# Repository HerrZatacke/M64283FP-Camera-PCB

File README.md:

# M64283FP Camera PCB

A PCB for mounting the M64283FP sensor to use it with a regular GameBoy Camera

With the revision from [24. Aug 2023](#24-aug-2023) it acts also as a good improvement against lightleaks when using the regular sensor ([Note this](#disclaimer)). 

This KiCad Project aims to replace the original GameBoy Camera Sensor PCB to allow using the alternative M64283FP sensor including accessing it's two extra pins `TADD` and `STRB`

## License
[MIT](LICENSE)

## Revision History
### 24. Aug 2023
  * Added Solderpoints for GND and VOUT
  * Changed PCB Shape to prevent light leaking
  * Changed footprints to prevent
### [08. Aug 2023](https://github.com/HerrZatacke/M64283FP-Camera-PCB/tree/d5482509ec9628336e77a40f23f6922016d4d017)
  * Initial Version

## Disclaimer
Attempt all modifications at your own risk. All sensors are highly sensitive to excessive heat. SMD projects are not for beginners. Use common sense. 

## Links
- Thanks to [Raphaël Boichot](https://github.com/Raphael-Boichot/) for starting the project.
- Visit the [Game Boy Gamera Club Discord](https://discord.gg/C7WFJHG) for discussions.
- Mitsubishi [M64282FP Sensor Datasheet](https://pdf1.alldatasheet.com/datasheet-pdf/view/146598/MITSUBISHI/M64282FP.html) (original sensor)
- Mitsubishi [M64283FP Sensor Datasheet](https://pdf1.alldatasheet.com/datasheet-pdf/view/89637/MITSUBISHI/M64283FP.html) (replacement sensor)

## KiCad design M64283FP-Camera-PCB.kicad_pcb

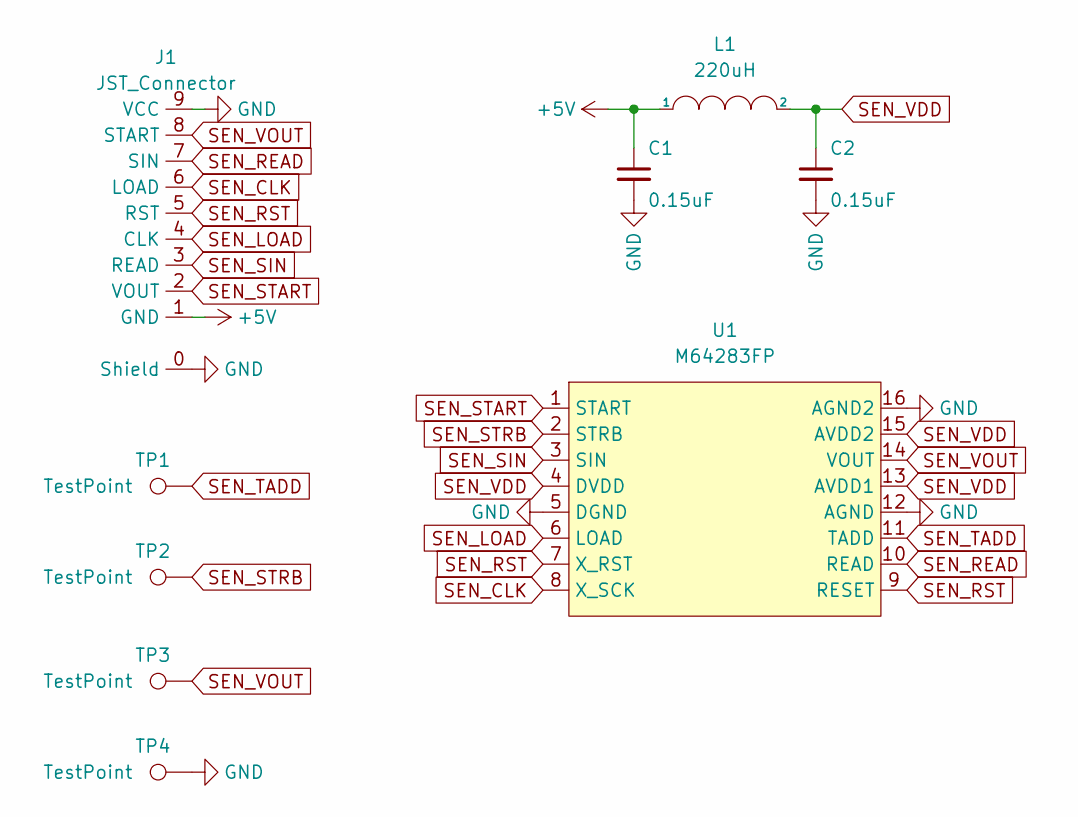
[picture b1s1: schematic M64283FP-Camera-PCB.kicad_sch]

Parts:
C1, C2: 0.15uF; 0603_HandSolder (LP)
J1: JST_Connector; JST Connector (LP)
L1: 220uH; 1210_HandSolder (LP)
TP1, TP2, TP3, TP4: TestPoint; TestPoint_Pad_1.5x1.5mm (LP)
U1: M64283FP; M6428xFP (LP)

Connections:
+5V: C1.1, J1.1 (GND), L1.1
GND: C1.2, C2.2, J1.0 (Shield), J1.9 (VCC), TP4.1, U1.5 (DGND), U1.12 (AGND), U1.16 (AGND2)
SEN_CLK: J1.6 (LOAD), U1.8 (X_SCK)
SEN_LOAD: J1.4 (CLK), U1.6 (LOAD)
SEN_READ: J1.7 (SIN), U1.10 (READ)
SEN_RST: J1.5 (RST), U1.7 (X_RST), U1.9 (RESET)
SEN_SIN: J1.3 (READ), U1.3 (SIN)
SEN_START: J1.2 (VOUT), U1.1 (START)
SEN_STRB: TP2.1, U1.2 (STRB)
SEN_TADD: TP1.1, U1.11 (TADD)
SEN_VDD: C2.1, L1.2, U1.4 (DVDD), U1.13 (AVDD1), U1.15 (AVDD2)
SEN_VOUT: J1.8 (START), TP3.1, U1.14 (VOUT)

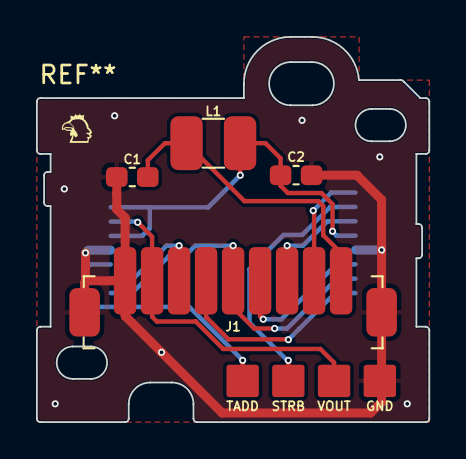
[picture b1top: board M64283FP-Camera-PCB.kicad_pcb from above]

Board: 2 copper layers, 21.8 x 21.4 mm, 9 parts (1 on the bottom side), 12 nets.

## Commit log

2023-08-07 Initial project data
2023-08-07 Add logo
2023-08-07 Add preview image Optimize labels
2023-08-07 Add Readme
2023-08-24 Add LightProof (LP) footprints
2023-08-24 Update Logo
2023-08-24 Update project with new footprints and PCB shape
2023-08-24 Caches
2023-08-24 Fix link
2023-08-24 Add Lightproof testpoint
2023-08-24 Correct link
